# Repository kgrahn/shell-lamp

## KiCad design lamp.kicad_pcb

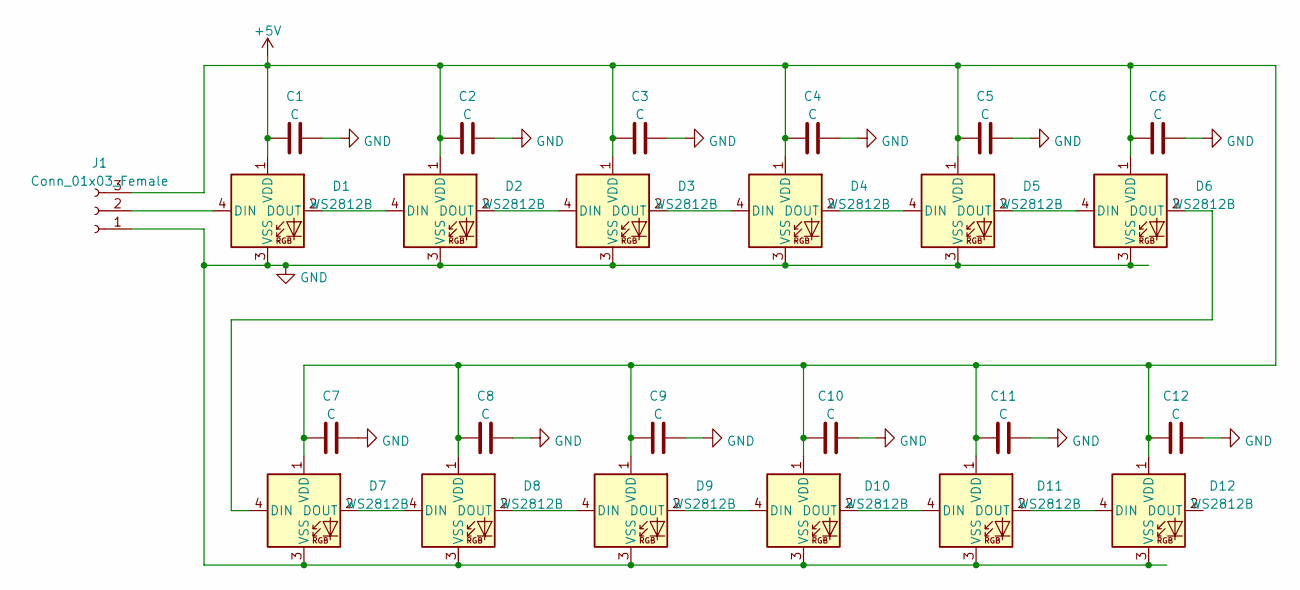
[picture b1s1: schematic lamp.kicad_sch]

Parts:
C1, C2, C3, C4, C5, C6, C7, C8, C9, C10, C11, C12: C; C_0603_1608Metric_Pad1.08x0.95mm_HandSolder
D1, D2, D3, D4, D5, D6, D7, D8, D9, D10, D11, D12: WS2812B; LED_WS2812B_PLCC4_5.0x5.0mm_P3.2mm
J1: Conn_01x03_Female; PinHeader_1x03_P2.54mm_Vertical

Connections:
+5V: C1.1, C2.1, C3.1, C4.1, C5.1, C6.1, C7.1, C8.1, C9.1, C10.1, C11.1, C12.1, D1.1 (VDD), D2.1 (VDD), D3.1 (VDD), D4.1 (VDD), D5.1 (VDD), D6.1 (VDD), D7.1 (VDD), D8.1 (VDD), D9.1 (VDD), D10.1 (VDD), D11.1 (VDD), D12.1 (VDD), J1.3
GND: C1.2, C2.2, C3.2, C4.2, C5.2, C6.2, C7.2, C8.2, C9.2, C10.2, C11.2, C12.2, D1.3 (VSS), D2.3 (VSS), D3.3 (VSS), D4.3 (VSS), D5.3 (VSS), D6.3 (VSS), D7.3 (VSS), D8.3 (VSS), D9.3 (VSS), D10.3 (VSS), D11.3 (VSS), D12.3 (VSS), J1.1
unnamed: D1.2 (DOUT), D2.4 (DIN)
unnamed: D1.4 (DIN), J1.2
unnamed: D2.2 (DOUT), D3.4 (DIN)
unnamed: D3.2 (DOUT), D4.4 (DIN)
unnamed: D4.2 (DOUT), D5.4 (DIN)
unnamed: D5.2 (DOUT), D6.4 (DIN)
unnamed: D6.2 (DOUT), D7.4 (DIN)
unnamed: D7.2 (DOUT), D8.4 (DIN)
unnamed: D8.2 (DOUT), D9.4 (DIN)
unnamed: D10.2 (DOUT), D11.4 (DIN)
unnamed: D9.2 (DOUT), D10.4 (DIN)
unnamed: D11.2 (DOUT), D12.4 (DIN)

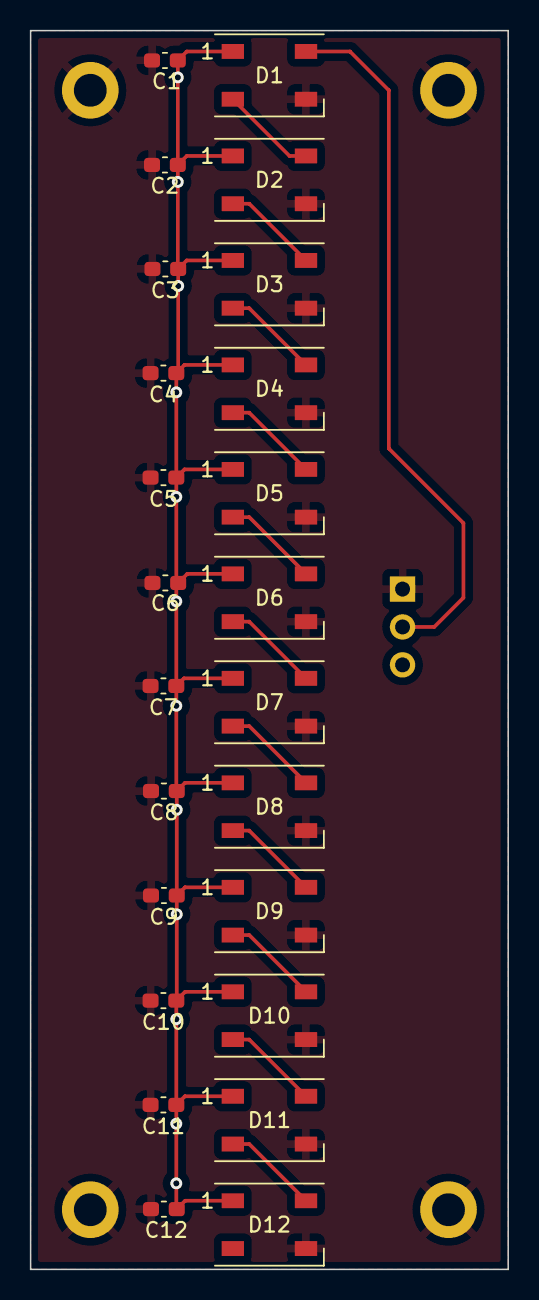
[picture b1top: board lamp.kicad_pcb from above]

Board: 2 copper layers, 32.0 x 83.0 mm, 25 parts (1 on the bottom side), 14 nets.

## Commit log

2022-09-18 added lamp
2022-09-18 updated with bom and outline
2022-09-18 updated fab output with dimensions
